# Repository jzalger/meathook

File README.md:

# Meat Hook

Meat Hook is a temperature and humidity controlled fridge for dry aging meat.
This project goes through designing the circuit and PCB as well as the surrounding full-stack web application and data
logging utilities. It also explores using various control algorithms including basic, PID, and machine learning approaches.

The controller is based on the [Particle Photon](http://www.particle.io), a Wifi enabled ARM based processor with a cloud-based API.
The web application backend is written in Python using the Flask framework. The frontend uses HTML and Javascript, leveraging the Bootstrap framework.

## Circuit and PCB Design

Below is a simple block diagram showing the sensors and actuators in the fridge.

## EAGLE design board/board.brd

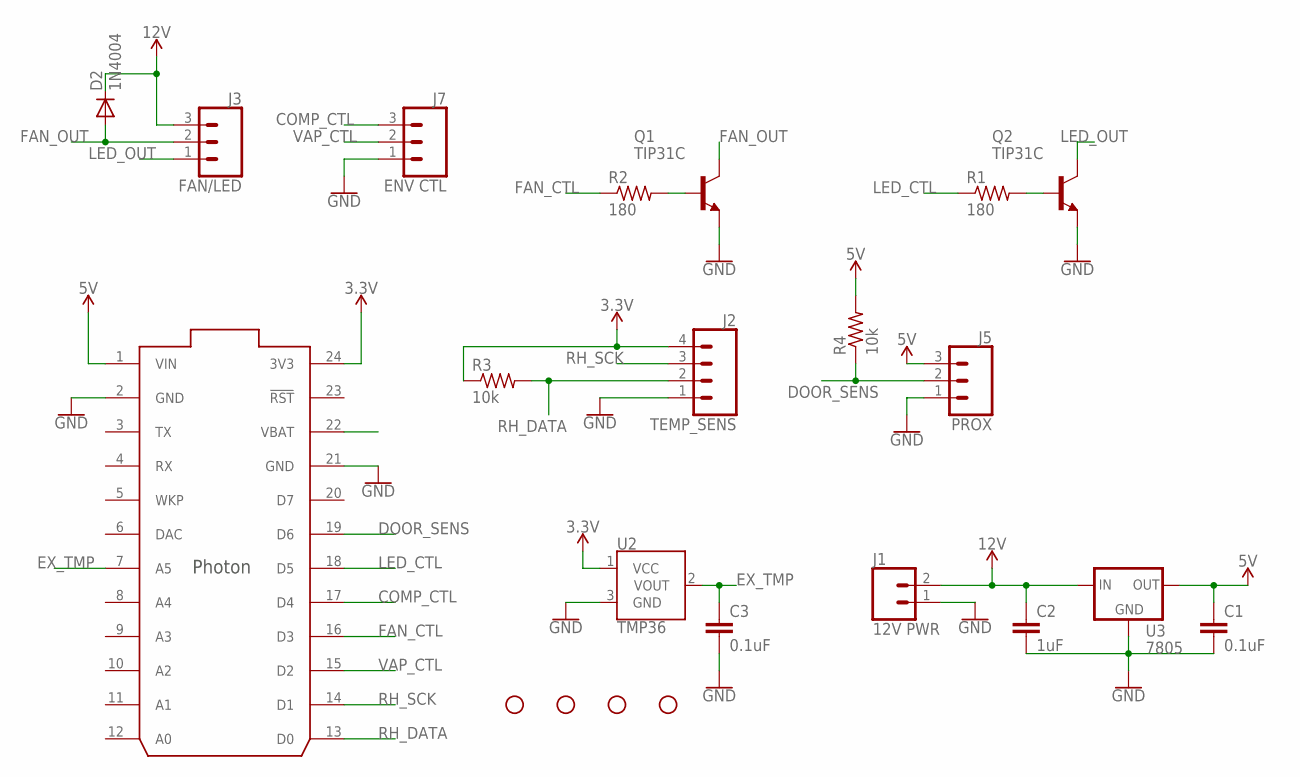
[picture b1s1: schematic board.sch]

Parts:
C1, C3: 0.1uF; CAP-PTH-SMALL-KIT
C2: 1uF; CAP-PTH-SMALL-KIT
D2: 1N4004; DO41-10
H1, H2, H3, H4: STAND-OFF
J1: 12V PWR; SCREWTERMINAL-3.5MM-2
J2: TEMP_SENS; SCREWTERMINAL-3.5MM-4_LOCK
J3: FAN/LED; SCREWTERMINAL-5MM-3
J5: PROX; SCREWTERMINAL-5MM-3
J7: ENV CTL; SCREWTERMINAL-5MM-3
Q1, Q2: TIP31C; TO220
R1, R2: 180; 0207/10
R3, R4: 10k; 0207/10
U2: TMP36; TO-92
U3: 7805; TO-220-ALT
U$1: PHOTON_SMD

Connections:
3.3V: J2.4, R3.1, U2.1 (VCC), U$1.24 (3V3)
5V: C1.1, J5.3, R4.2, U3.OUT, U$1.1 (VIN)
12V: C2.1, D2.C, J1.2, J3.3, U3.IN
COMP_CTL: J7.3, U$1.17 (D4)
DOOR_SENS: J5.2, R4.1, U$1.19 (D6)
EX_TMP: C3.1, U2.2 (VOUT), U$1.7 (A5)
FAN_CTL: R2.1, U$1.16 (D3)
FAN_OUT: D2.A, J3.2, Q1.2 (C)
GND: C1.2, C2.2, C3.2, J1.1, J2.1, J5.1, J7.1, Q1.3 (E), Q2.3 (E), U2.3 (GND), U3.GND, U$1.2 (GND), U$1.21 (GND)
LED_CTL: R1.1, U$1.18 (D5)
LED_OUT: J3.1, Q2.2 (C)
unnamed: Q2.1 (B), R1.2
unnamed: Q1.1 (B), R2.2
RH_DATA: J2.2, R3.2, U$1.13 (D0)
RH_SCK: J2.3, U$1.14 (D1)
VAP_CTL: J7.2, U$1.15 (D2)

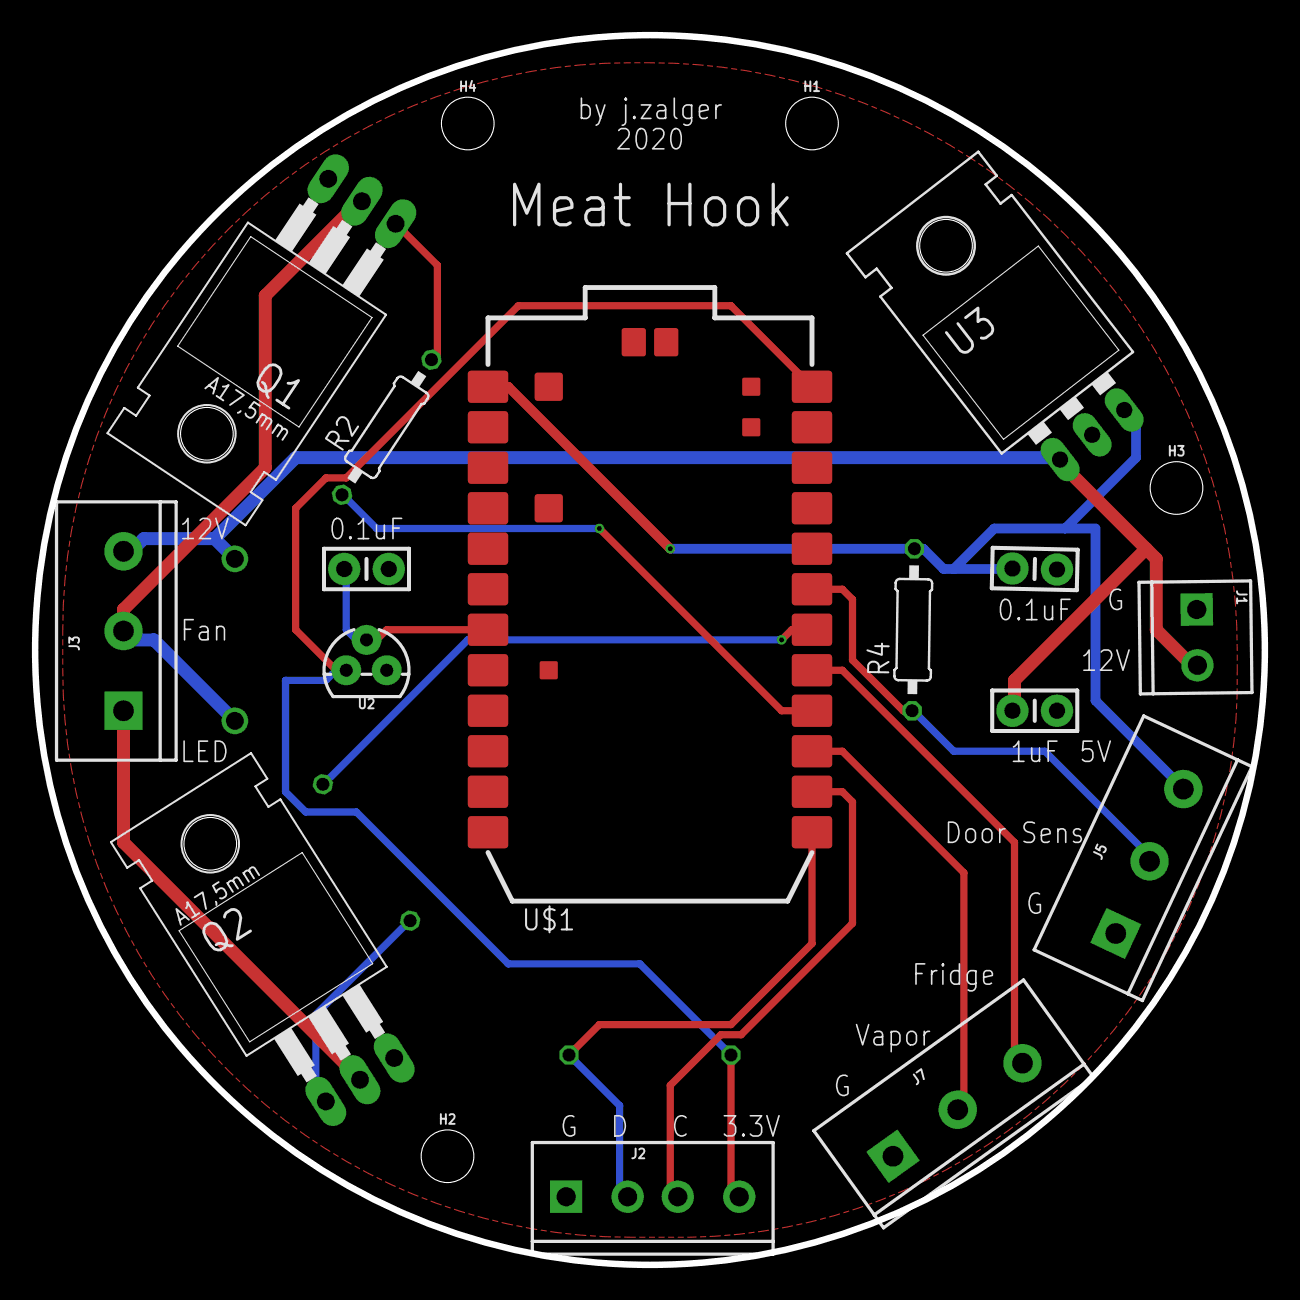
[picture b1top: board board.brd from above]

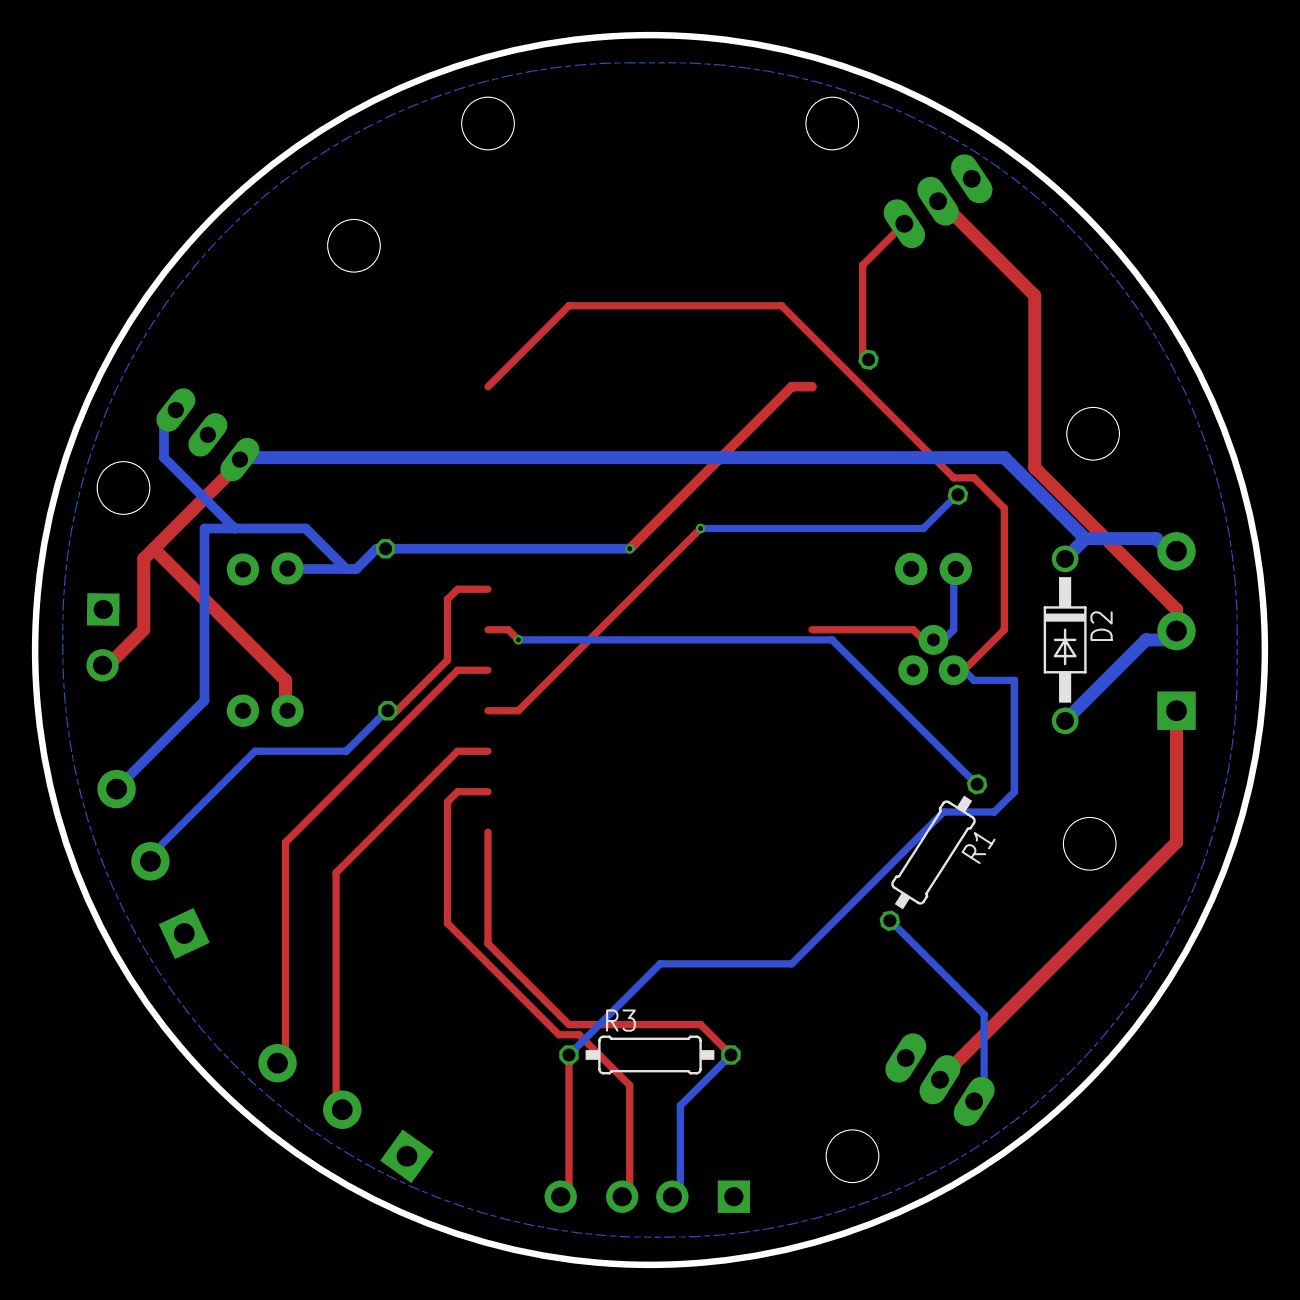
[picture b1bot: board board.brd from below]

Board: 2 copper layers, 77.1 x 77.1 mm, 22 parts (3 on the bottom side), 16 nets.

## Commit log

2020-05-16 Scaffolding.
2020-05-17 logging implementation
2020-05-17 logging refactoring
2020-05-17 logging query bug fixes
2020-05-17 updates to influx parsing
2020-05-17 Functional data logging to influxdb
2020-05-20 added firmware files
2020-05-21 Fixed bug with influx db type mismatch
2020-05-22 Frontend mockups and some backend rough in
2020-05-22 Added board, schematic, and gerbers
2020-05-22 Added pcb and schematic images
2020-05-22 Added images to README.md
2020-05-22 Minor readme updates
2020-05-22 Frontend updates with server side rendering of state Refactored css and template Minor backend updates
2020-05-22 Frontend updates
2020-05-23 - Added device control class - Backend updates.
2020-05-24 - control wiring
2020-05-25 refactoring meathook class to update state based on stream events
2020-05-25 template updates
2020-05-25 More refactoring, back to client side state loading.
2020-05-25 - Started client side state init. - Fixed java and jquery bugs - Basic init working
2020-05-25 - Javascript state init fully implemented
2020-05-25 - added temp and rh control funcs to firmware - Working java implementations for setpoints and tmp control
2020-05-25 - added temp and rh control funcs to firmware - Working java implementations of most controls
2020-05-26 - various bug fixes and firmware updates - alarm UI not working well. need to subscribe to the alarm event feeds and make the returned values consistent. Check the js alarm parsing as well.
2020-05-26 Fixed alarms
2020-05-26 Cleaning
2020-05-26 updated host info
2020-05-27 - fixed responsive sizing issue - Fixed progress bar scaling with values - JS refactoring
2020-05-27 More JS refactoring
2020-05-27 Readme updates
2020-05-31 - Added ui for energy saving - Disabled humidity controls
2020-11-21 - Added static image to UI
2020-11-21 - Implemented live stream backend with LED control
2020-11-21 bug fixes and stream rotate
2020-11-21 more bug fixes
2021-01-22 Containerization
2022-08-03 Refactoring to align with new deployment standards
2022-08-04 Backend refactoring round 1
2022-08-04 Frontend and JS refactoring
2022-08-04 Web app performance improvements
2022-08-04 refactoring firmware
2022-08-05 Fixed bugs with boolean state transmission, javascript irregularities
2022-08-05 Added ui elements for overnight energy saving, disconnect status
2022-08-05 git magic
2022-08-09 Updates to energy saving implementation
2022-08-09 Expanded unit tests
2022-08-09 Fixed HTML Dark Mode
2022-08-10 bug fixes to javascript
2022-08-10 Added sonarcube properties
2022-08-10 Fixed git commit problems erasing html updates
2022-08-10 More HTML fixes
2022-08-10 CI updates
2022-08-10 Updates to CI workflow and readme
2022-08-10 test update
2022-08-10 pipfile updates for dev packages
2022-08-10 HTML updates and test refactoring
2022-08-10 Test refactoring
2022-08-10 Fixes to es settings and JS bug fixes
2022-08-10 Fixed ES controls
2022-08-10 Added force state refresh button
2022-08-10 Baseline unit tests
2022-08-10 integration test updates
2022-08-11 test updates
2022-08-11 Updates to CI pipeline and lint fixes
2022-08-11 More git env updates
2022-08-11 pipeline fixes
2022-08-11 gunicorn fix
2022-08-11 Added syslog config, refactored Flask app naming
2022-08-11 Expanded logging capability
2022-08-11 Big fixes to test suite
2022-08-11 Fixed wsgi issue
2022-08-11 Fixed gunicorn issue
2022-08-12 Updates to integration tests
2022-12-09 Bump certifi from 2022.6.15 to 2022.12.7
    Bumps [certifi](https://github.com/certifi/python-certifi) from 2022.6.15 to 2022.12.7.
    - [Release notes](https://github.com/certifi/python-certifi/releases)
    - [Commits](https://github.com/certifi/python-certifi/compare/2022.06.15...2022.12.07)
    ---
    updated-dependencies:
    - dependency-name: certifi
2023-02-16 Bump werkzeug from 2.2.2 to 2.2.3
    Bumps [werkzeug](https://github.com/pallets/werkzeug) from 2.2.2 to 2.2.3.
    - [Release notes](https://github.com/pallets/werkzeug/releases)
    - [Changelog](https://github.com/pallets/werkzeug/blob/main/CHANGES.rst)
    - [Commits](https://github.com/pallets/werkzeug/compare/2.2.2...2.2.3)
    ---
    updated-dependencies:

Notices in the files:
parts and their libraries:
SparkFun-Capacitors: Licensing: Creative Commons ShareAlike 4.0 International - https://creativecommons.org/licenses/by-sa/4.0
Particle-Devices: Licensing: Designed by Particle.
